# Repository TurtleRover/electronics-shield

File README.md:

<p align="center">
  
</p>
<h1 align="center">Electronics: Shield</h1>
<h4 align="center">This is Raspberry Pi 3 hat designed for Turtle rover.</h4>  

<p align="center">

</p>
<p align="center">
  <a href="http://turtlerover.com" alt="Website">Website</a> |
  <a href="https://www.facebook.com/TurtleRover/" alt="Facebook">Facebook</a> |
  <a href="https://www.youtube.com/channel/UCxukvEct3wP0S5FACa3uelA" alt="YouTube">YouTube</a>
</p>

## Specification:

Supply voltage: from 12 V to 28 V  
Equipped with TLE9201SG motor controllers  
Continuous output current per channel: 6 A  
Maximum momentary current per channel: 8 A  
Number of channels: 4  
PWM frequency: up to 20 kHz  
3 x adjustable step-down DC-DC 3A converters   
Built-in STM32F030 microprocessor  
Available interfaces:  
- I2C/UART
- SPI
- USB
- SWD
- 3 x servo

Dedicated to Raspberry Pi B + connectors  
Dimensions: 84 x 56 mm

## Board view

## Connectors standard  

| I2C & Servo  | USB & SPI | Programming  |
| ------------- | ------------- | ------------- |
|   |   |  |

## Manufacturing
Manufacture files are generated and added to release.

### Online view of schematics and layout
View this project on [CADLAB.io](https://cadlab.io/project/1250). 

This git project is intended for using with Eagle PCB.

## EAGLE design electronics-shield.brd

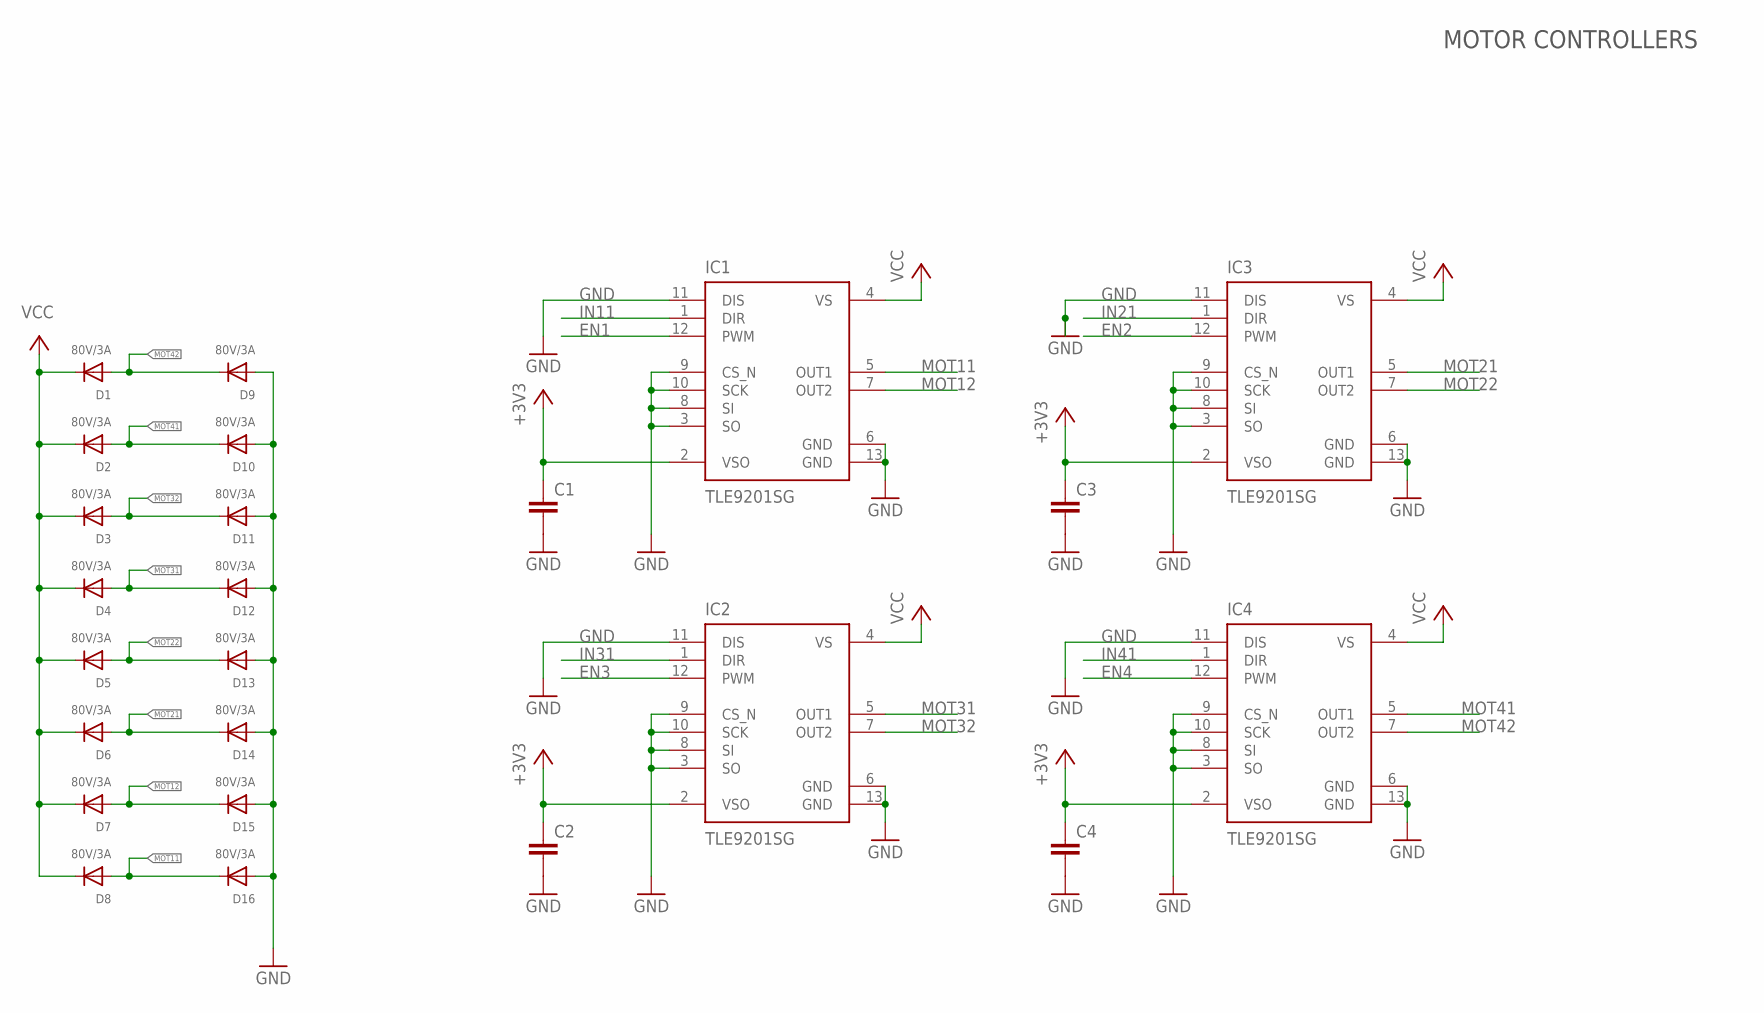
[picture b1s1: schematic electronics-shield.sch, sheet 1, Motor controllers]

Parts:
C1, C2, C3, C4: CAPACITOR_SMD_0603; C0603K
D1, D2, D3, D4, D5, D6, D7, D8, D9, D10, D11, D12, D13, D14, D15, D16: 80V/3A; SOD-123FL
IC1, IC2, IC3, IC4: TLE9201SG; PG-DSO-12-9

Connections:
+3V3: C1.1, C2.1, C3.1, C4.1, IC1.2 (VSO), IC2.2 (VSO), IC3.2 (VSO), IC4.2 (VSO); also elsewhere on the board
EN1: IC1.12 (PWM); also elsewhere on the board
EN2: IC3.12 (PWM); also elsewhere on the board
EN3: IC2.12 (PWM); also elsewhere on the board
EN4: IC4.12 (PWM); also elsewhere on the board
GND: C1.2, C2.2, C3.2, C4.2, D9.A, D10.A, D11.A, D12.A, D13.A, D14.A, D15.A, D16.A, IC1.3 (SO), IC1.6 (GND), IC1.8 (SI), IC1.9 (CS_N), IC1.10 (SCK), IC1.11 (DIS), IC1.13 (GND), IC2.3 (SO), IC2.6 (GND), IC2.8 (SI), IC2.9 (CS_N), IC2.10 (SCK), IC2.11 (DIS), IC2.13 (GND), IC3.3 (SO), IC3.6 (GND), IC3.8 (SI), IC3.9 (CS_N), IC3.10 (SCK), IC3.11 (DIS), IC3.13 (GND), IC4.3 (SO), IC4.6 (GND), IC4.8 (SI), IC4.9 (CS_N), IC4.10 (SCK), IC4.11 (DIS), IC4.13 (GND); also elsewhere on the board
IN11: IC1.1 (DIR); also elsewhere on the board
IN21: IC3.1 (DIR); also elsewhere on the board
IN31: IC2.1 (DIR); also elsewhere on the board
IN41: IC4.1 (DIR); also elsewhere on the board
MOT11: D8.A, D16.C, IC1.5 (OUT1); also elsewhere on the board
MOT12: D7.A, D15.C, IC1.7 (OUT2); also elsewhere on the board
MOT21: D6.A, D14.C, IC3.5 (OUT1); also elsewhere on the board
MOT22: D5.A, D13.C, IC3.7 (OUT2); also elsewhere on the board
MOT31: D4.A, D12.C, IC2.5 (OUT1); also elsewhere on the board
MOT32: D3.A, D11.C, IC2.7 (OUT2); also elsewhere on the board
MOT41: D2.A, D10.C, IC4.5 (OUT1); also elsewhere on the board
MOT42: D1.A, D9.C, IC4.7 (OUT2); also elsewhere on the board
VCC: D1.C, D2.C, D3.C, D4.C, D5.C, D6.C, D7.C, D8.C, IC1.4 (VS), IC2.4 (VS), IC3.4 (VS), IC4.4 (VS); also elsewhere on the board

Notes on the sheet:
MOTOR CONTROLLERS

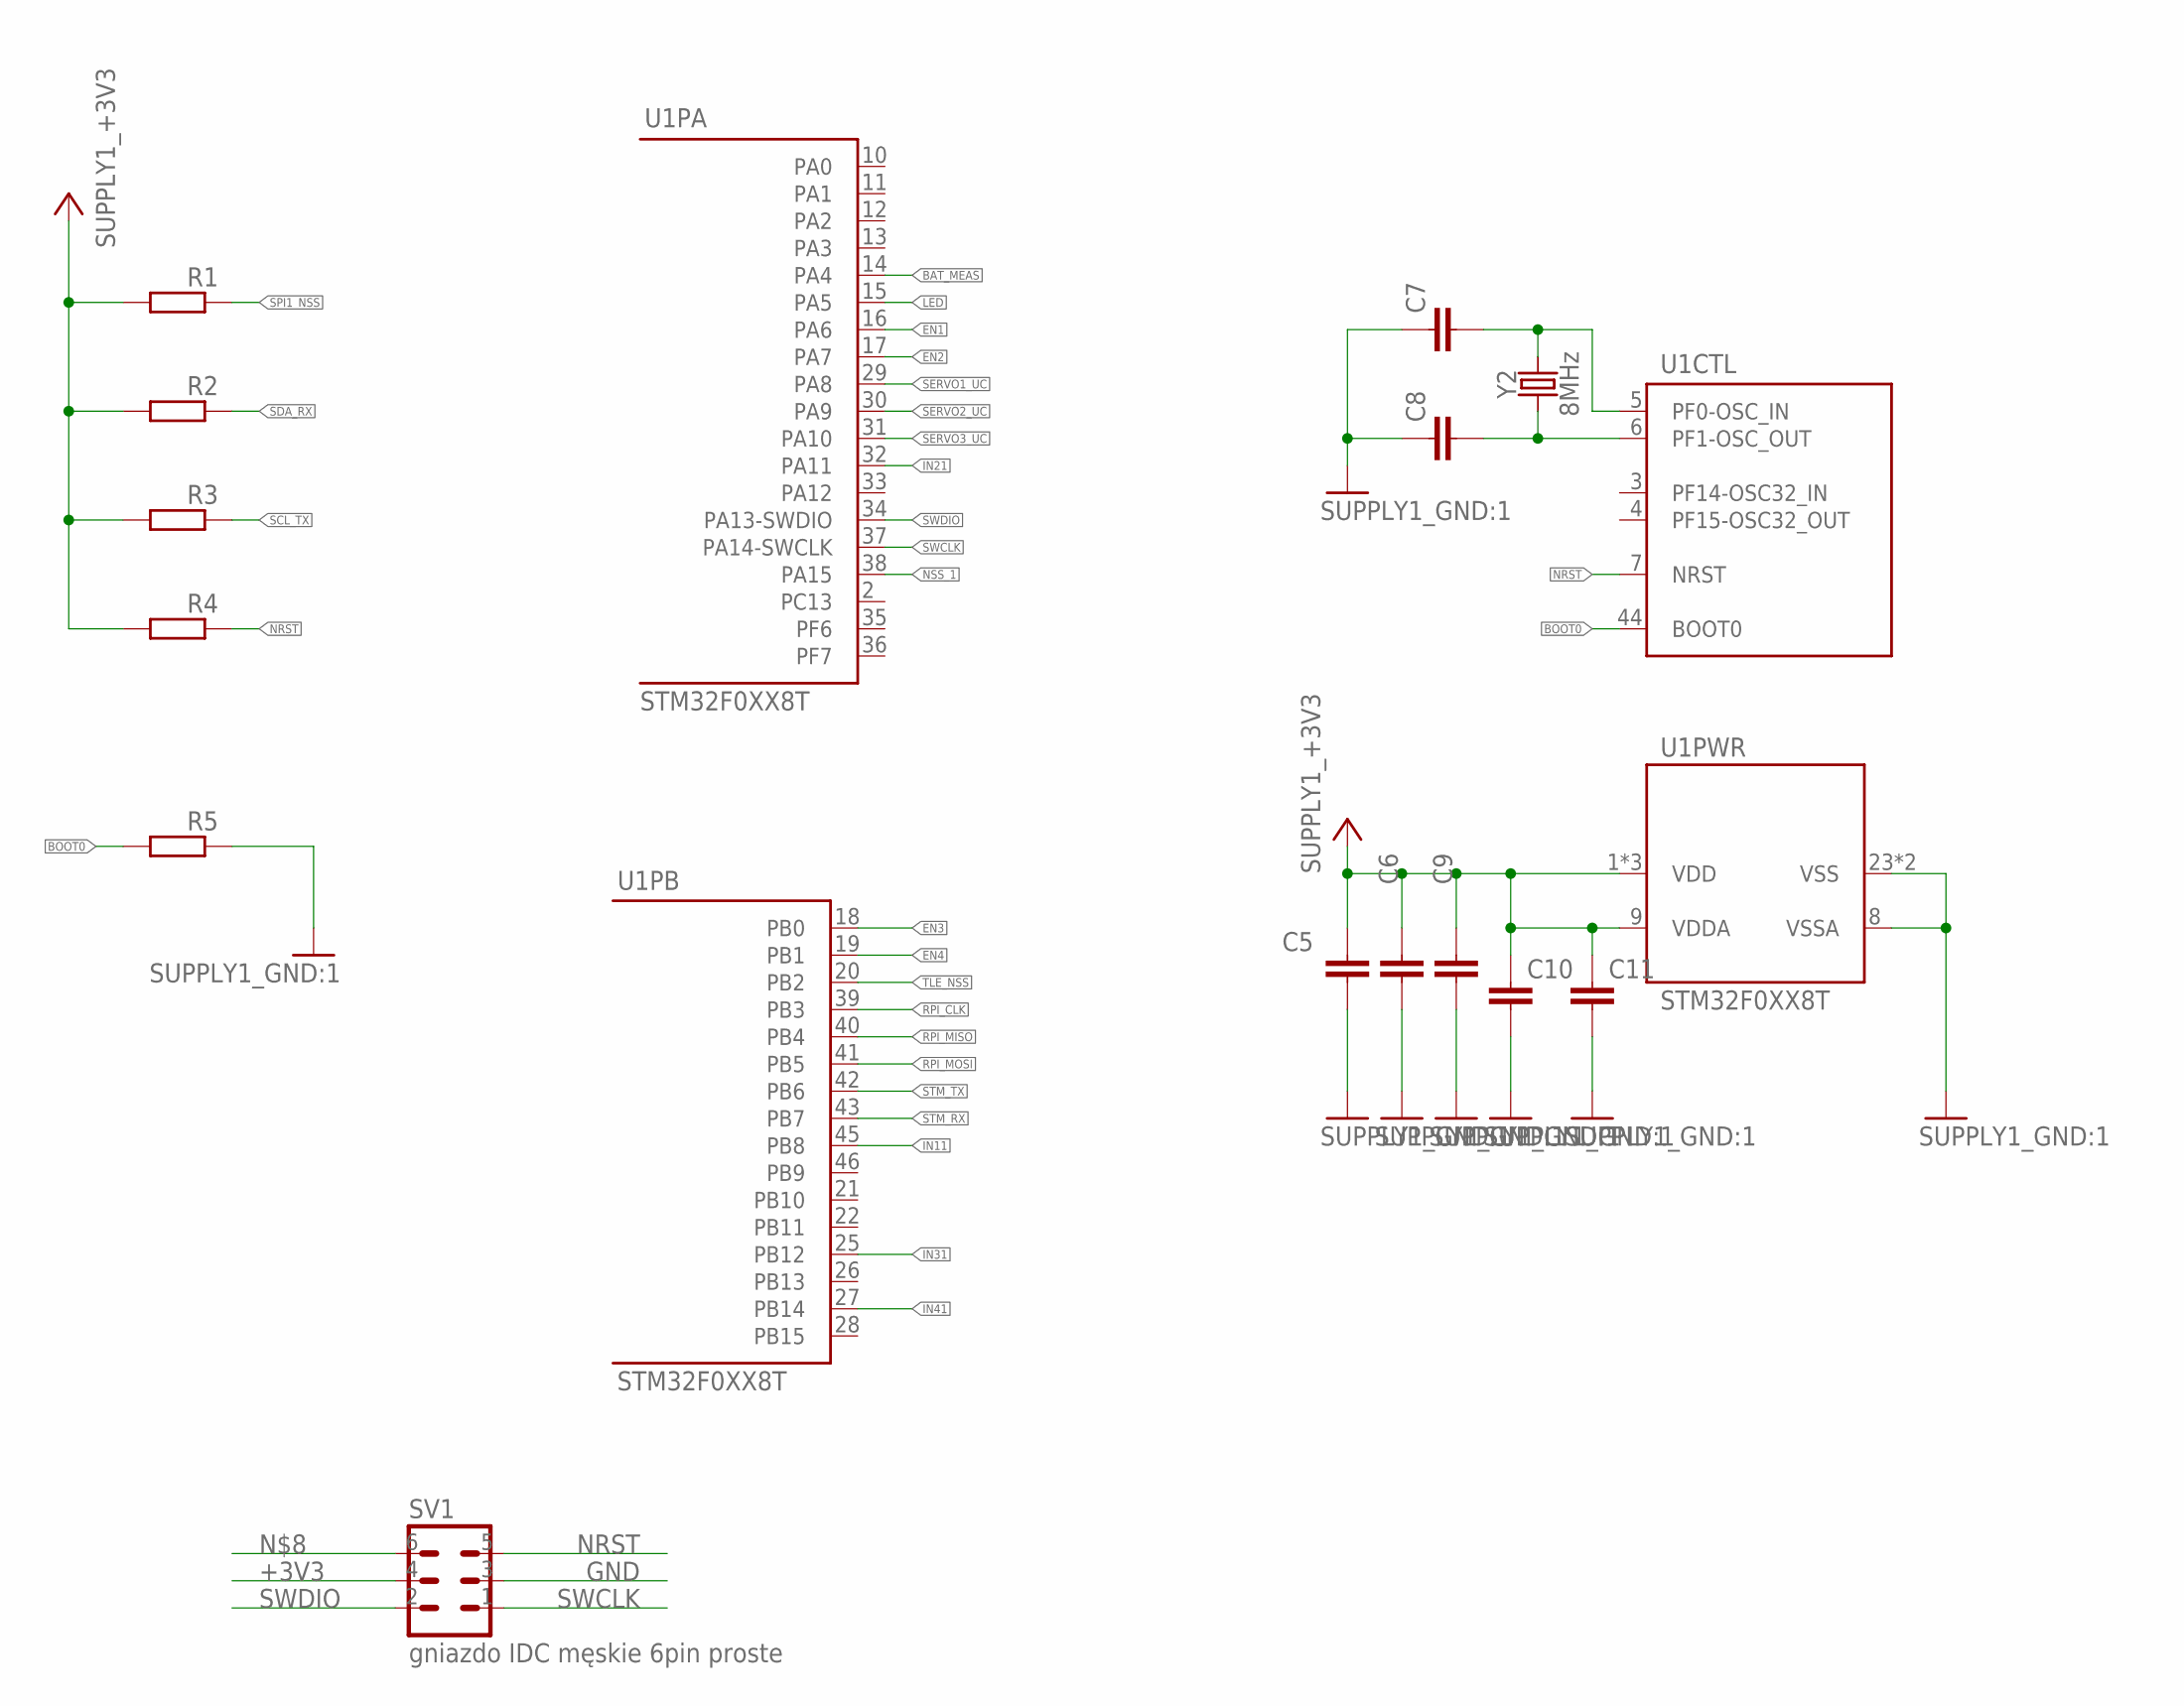
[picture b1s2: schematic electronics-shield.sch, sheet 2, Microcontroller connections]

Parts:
C5, C6, C7, C8, C9, C10, C11: CAPACITOR_SMD_0603; C0603K
R1, R2, R3, R4, R5: RESISTOR_SMD_0603; R0603
SV1: gniazdo IDC męskie 6pin proste; ML6
U1: STM32F0XX8T; LQFP48
Y2: 8MHz; CRYSTAL-SMD-5X3.2-4PAD

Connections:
+3V3: C5.1, C6.1, C9.1, C10.1, C11.1, R1.2, R2.2, R3.2, R4.2, SV1.4, U1.1 (VDD), U1.9 (VDDA), U1.24 (VDD), U1.48 (VDD); also elsewhere on the board
BAT_MEAS: U1.14 (PA4); also elsewhere on the board
BOOT0: R5.2, U1.44 (BOOT0)
EN1: U1.16 (PA6); also elsewhere on the board
EN2: U1.17 (PA7); also elsewhere on the board
EN3: U1.18 (PB0); also elsewhere on the board
EN4: U1.19 (PB1); also elsewhere on the board
GND: C5.2, C6.2, C7.1, C8.1, C9.2, C10.2, C11.2, R5.1, SV1.3, U1.8 (VSSA), U1.23 (VSS), U1.47 (VSS); also elsewhere on the board
IN11: U1.45 (PB8); also elsewhere on the board
IN21: U1.32 (PA11); also elsewhere on the board
IN31: U1.25 (PB12); also elsewhere on the board
IN41: U1.27 (PB14); also elsewhere on the board
LED: U1.15 (PA5); also elsewhere on the board
NRST: R4.1, SV1.5, U1.7 (NRST); also elsewhere on the board
NSS_1: U1.38 (PA15); also elsewhere on the board
OSCILATOR_N: C7.2, U1.5 (PF0-OSC_IN), Y2.3 (2)
OSCILATOR_P: C8.2, U1.6 (PF1-OSC_OUT), Y2.1
RPI_CLK: U1.39 (PB3); also elsewhere on the board
RPI_MISO: U1.40 (PB4); also elsewhere on the board
RPI_MOSI: U1.41 (PB5); also elsewhere on the board
SCL_TX: R3.1; also elsewhere on the board
SDA_RX: R2.1; also elsewhere on the board
SERVO1_UC: U1.29 (PA8); also elsewhere on the board
SERVO2_UC: U1.30 (PA9); also elsewhere on the board
SERVO3_UC: U1.31 (PA10); also elsewhere on the board
SPI1_NSS: R1.1
STM_RX: U1.43 (PB7); also elsewhere on the board
STM_TX: U1.42 (PB6); also elsewhere on the board
SWCLK: SV1.1, U1.37 (PA14-SWCLK); also elsewhere on the board
SWDIO: SV1.2, U1.34 (PA13-SWDIO); also elsewhere on the board
TLE_NSS: U1.20 (PB2)

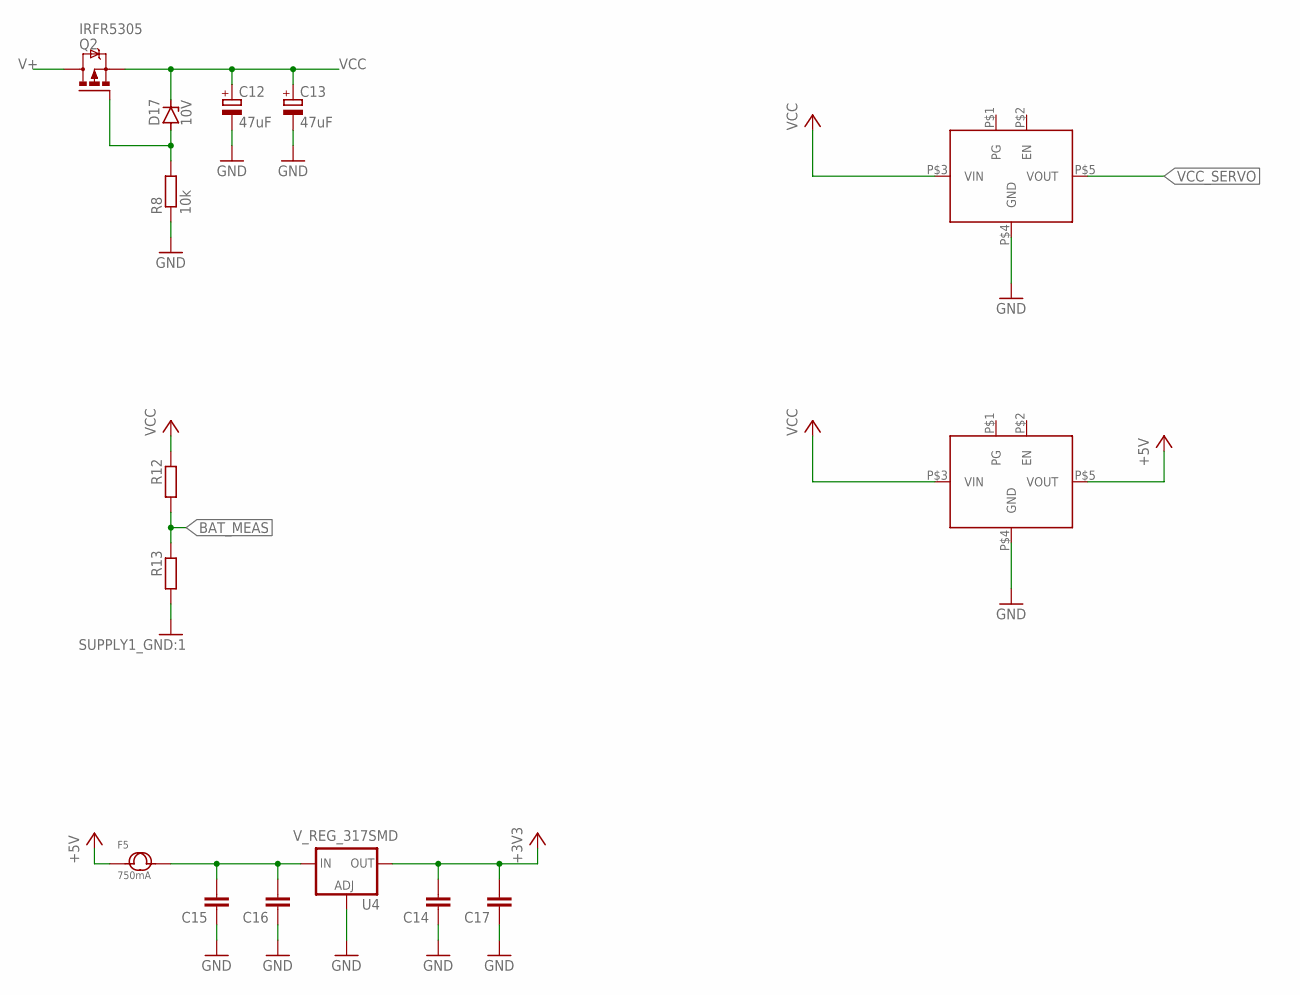
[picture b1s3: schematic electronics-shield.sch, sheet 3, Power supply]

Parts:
C12, C13: 47uF; PANASONIC_C
C14, C15, C16, C17: CAPACITOR_SMD_0603; C0603K
D17: 10V; SOD80C
F5: 750mA; F1206
Q2: IRFR5305; D-PAK_TO252AA
R8: 10k; R0603
R12, R13: RESISTOR_SMD_0603; R0603
U4: V_REG_317SMD; SOT223
U$1, U$2: POLOLU_D24V22FX

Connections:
+3V3: C14.2, C17.2, U4.2 (OUT); also elsewhere on the board
+5V: F5.1, U$2.P$5 (VOUT); also elsewhere on the board
BAT_MEAS: R12.2, R13.1; also elsewhere on the board
GND: C12.-, C13.-, C14.1, C15.1, C16.1, C17.1, R8.1, R13.2, U4.1 (ADJ), U$1.P$4 (GND), U$2.P$4 (GND); also elsewhere on the board
unnamed: D17.A, Q2.1 (G), R8.2
unnamed: C15.2, C16.2, F5.2, U4.3 (IN)
V+: Q2.4 (D); also elsewhere on the board
VCC: C12.+, C13.+, D17.C, Q2.3 (S), R12.1, U$1.P$3 (VIN), U$2.P$3 (VIN); also elsewhere on the board
VCC_SERVO: U$1.P$5 (VOUT); also elsewhere on the board

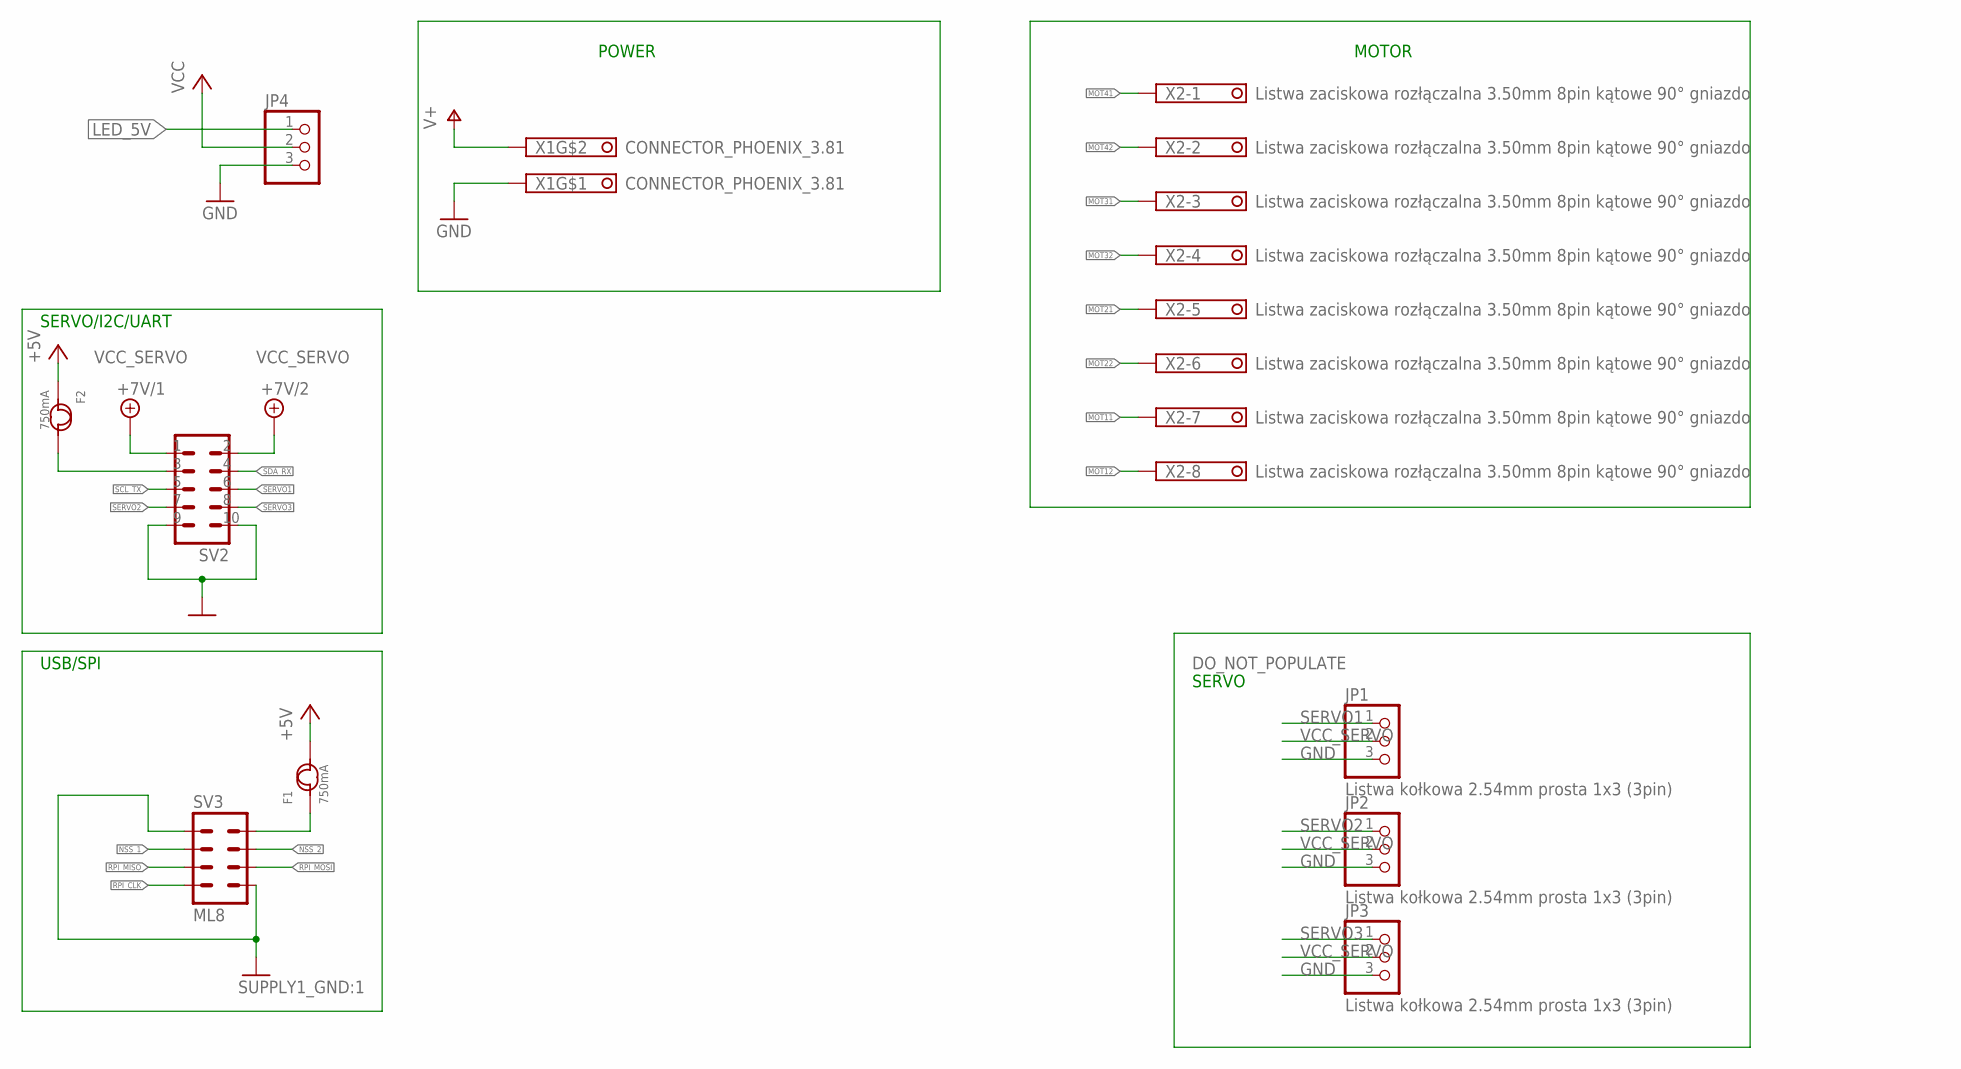
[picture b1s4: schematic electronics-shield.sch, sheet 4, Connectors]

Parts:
F1, F2: 750mA; F1206
JP1, JP2, JP3: Listwa kołkowa 2.54mm prosta 1x3 (3pin); 1X03_ROUND_DNP
JP4: PINHD-1X3; 1X03
SV2: ML10
SV3: ML8
X1: CONNECTOR_PHOENIX_3.81; 3.81MM_2PIN
X2: Listwa zaciskowa rozłączalna 3.50mm 8pin kątowe 9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; 3.5MM_8PIN

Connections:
+5V: F1.2, F2.1; also elsewhere on the board
GND: JP1.3, JP2.3, JP3.3, JP4.3, SV2.9, SV2.10, SV3.1, SV3.8, X1.1; also elsewhere on the board
LED_5V: JP4.1; also elsewhere on the board
MOT11: X2.7; also elsewhere on the board
MOT12: X2.8; also elsewhere on the board
MOT21: X2.5; also elsewhere on the board
MOT22: X2.6; also elsewhere on the board
MOT31: X2.3; also elsewhere on the board
MOT32: X2.4; also elsewhere on the board
MOT41: X2.1; also elsewhere on the board
MOT42: X2.2; also elsewhere on the board
unnamed: F2.2, SV2.3
unnamed: F1.1, SV3.2
NSS_1: SV3.3; also elsewhere on the board
NSS_2: SV3.4
RPI_CLK: SV3.7; also elsewhere on the board
RPI_MISO: SV3.5; also elsewhere on the board
RPI_MOSI: SV3.6; also elsewhere on the board
SCL_TX: SV2.5; also elsewhere on the board
SDA_RX: SV2.4; also elsewhere on the board
SERVO1: JP1.1, SV2.6; also elsewhere on the board
SERVO2: JP2.1, SV2.7; also elsewhere on the board
SERVO3: JP3.1, SV2.8; also elsewhere on the board
V+: X1.2; also elsewhere on the board
VCC: JP4.2; also elsewhere on the board
VCC_SERVO: JP1.2, JP2.2, JP3.2, SV2.1, SV2.2; also elsewhere on the board

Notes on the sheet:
SERVO
MOTOR
POWER
SERVO/I2C/UART
USB/SPI

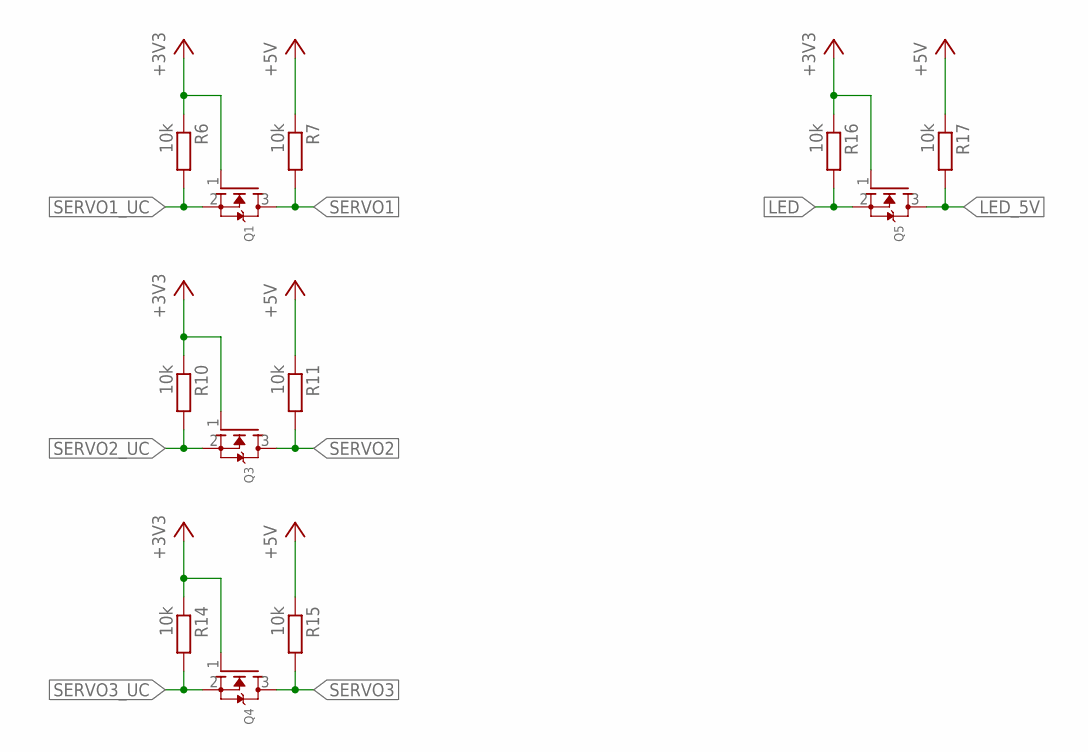
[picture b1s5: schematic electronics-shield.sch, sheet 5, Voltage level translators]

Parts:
Q1, Q3, Q4, Q5: MOSFET-NREFLOW; SOT23
R6, R7, R10, R11, R14, R15, R16, R17: 10k; R0603

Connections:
+3V3: Q1.1 (G), Q3.1 (G), Q4.1 (G), Q5.1 (G), R6.1, R10.1, R14.1, R16.1; also elsewhere on the board
+5V: R7.1, R11.1, R15.1, R17.1; also elsewhere on the board
LED: Q5.2 (S), R16.2; also elsewhere on the board
LED_5V: Q5.3 (D), R17.2; also elsewhere on the board
SERVO1: Q1.3 (D), R7.2; also elsewhere on the board
SERVO1_UC: Q1.2 (S), R6.2; also elsewhere on the board
SERVO2: Q3.3 (D), R11.2; also elsewhere on the board
SERVO2_UC: Q3.2 (S), R10.2; also elsewhere on the board
SERVO3: Q4.3 (D), R15.2; also elsewhere on the board
SERVO3_UC: Q4.2 (S), R14.2; also elsewhere on the board

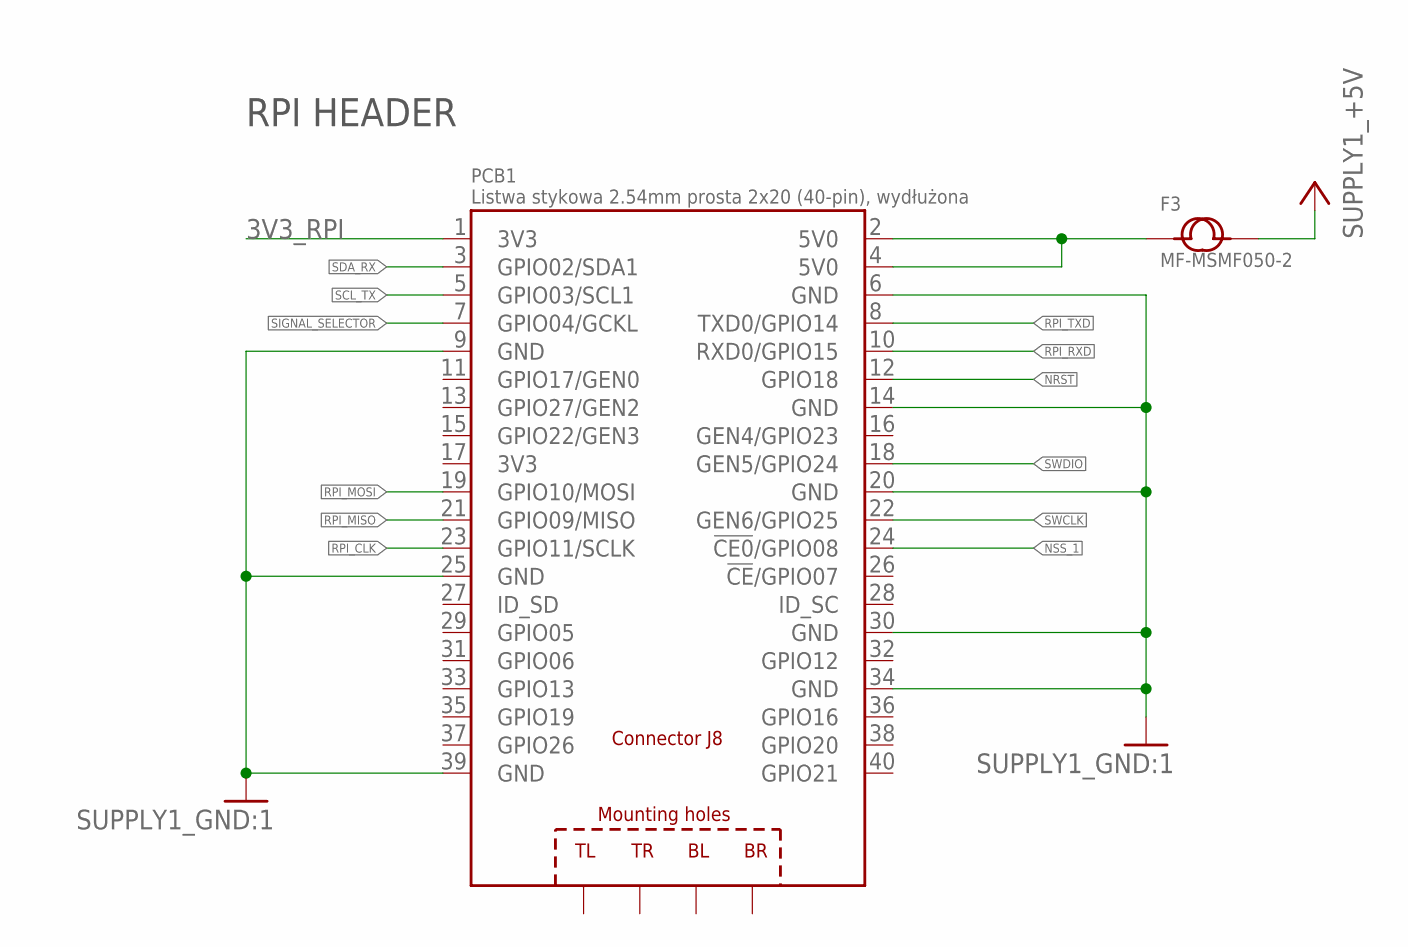
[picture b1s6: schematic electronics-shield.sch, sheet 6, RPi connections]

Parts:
F3: MF-MSMF050-2; F1812
PCB1: Listwa stykowa 2.54mm prosta 2x20 (40-pin), wydłu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; RASPBERRY_PI_B+_CONNECTOR_SMD

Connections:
3V3: PCB1.17 (3V3)
3V3_RPI: PCB1.1 (3V3)
+5V: F3.2; also elsewhere on the board
GND: PCB1.6 (GND), PCB1.9 (GND), PCB1.14 (GND), PCB1.20 (GND), PCB1.25 (GND), PCB1.30 (GND), PCB1.34 (GND), PCB1.39 (GND); also elsewhere on the board
unnamed: F3.1, PCB1.2 (5V0), PCB1.4 (5V0)
NRST: PCB1.12 (GPIO18); also elsewhere on the board
NSS_1: PCB1.24 (!CE0!/GPIO08); also elsewhere on the board
RPI_CLK: PCB1.23 (GPIO11/SCLK); also elsewhere on the board
RPI_MISO: PCB1.21 (GPIO09/MISO); also elsewhere on the board
RPI_MOSI: PCB1.19 (GPIO10/MOSI); also elsewhere on the board
RPI_RXD: PCB1.10 (RXD0/GPIO15); also elsewhere on the board
RPI_TXD: PCB1.8 (TXD0/GPIO14); also elsewhere on the board
SCL_TX: PCB1.5 (GPIO03/SCL1); also elsewhere on the board
SDA_RX: PCB1.3 (GPIO02/SDA1); also elsewhere on the board
SIGNAL_SELECTOR: PCB1.7 (GPIO04/GCKL); also elsewhere on the board
SWCLK: PCB1.22 (GEN6/GPIO25); also elsewhere on the board
SWDIO: PCB1.18 (GEN5/GPIO24); also elsewhere on the board

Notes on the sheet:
RPI HEADER

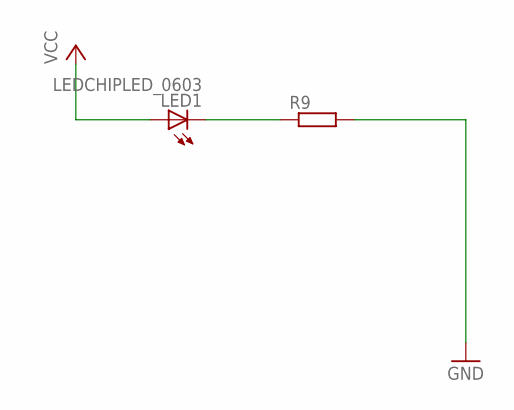
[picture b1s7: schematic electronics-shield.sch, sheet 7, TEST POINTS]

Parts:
LED1: LEDCHIPLED_0603; CHIPLED_0603
R9: RESISTOR_SMD_0603; R0603

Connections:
GND: R9.2; also elsewhere on the board
unnamed: LED1.C, R9.1
VCC: LED1.A; also elsewhere on the board

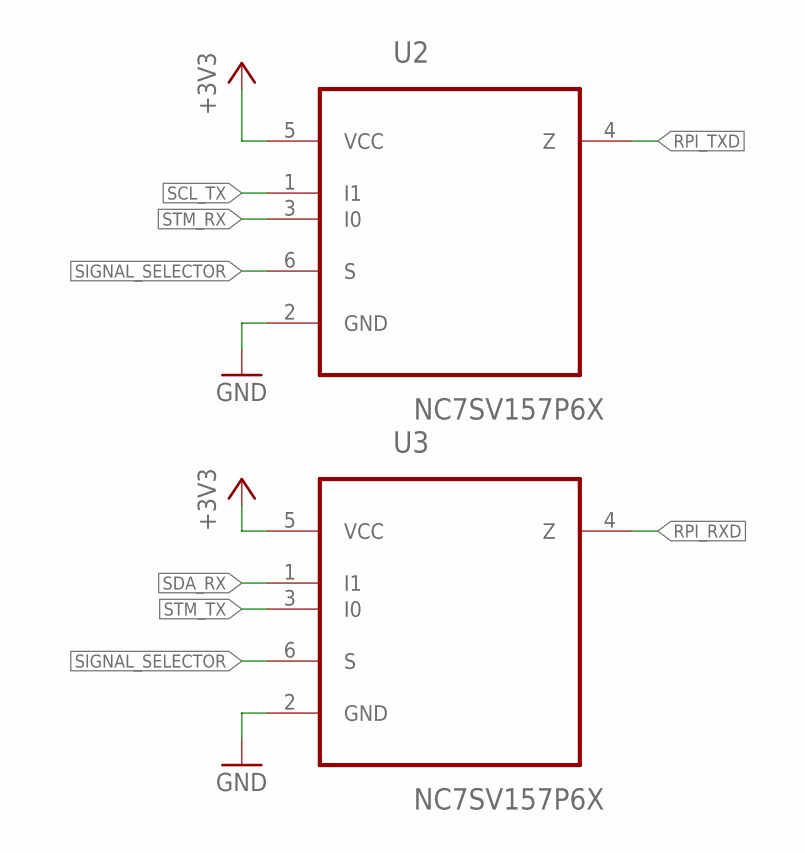
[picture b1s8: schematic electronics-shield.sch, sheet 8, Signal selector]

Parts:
U2, U3: NC7SV157P6X; SOT65P210X110-6N

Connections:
+3V3: U2.5 (VCC), U3.5 (VCC); also elsewhere on the board
GND: U2.2 (GND), U3.2 (GND); also elsewhere on the board
RPI_RXD: U3.4 (Z); also elsewhere on the board
RPI_TXD: U2.4 (Z); also elsewhere on the board
SCL_TX: U2.1 (I1); also elsewhere on the board
SDA_RX: U3.1 (I1); also elsewhere on the board
SIGNAL_SELECTOR: U2.6 (S), U3.6 (S); also elsewhere on the board
STM_RX: U2.3 (I0); also elsewhere on the board
STM_TX: U3.3 (I0); also elsewhere on the board

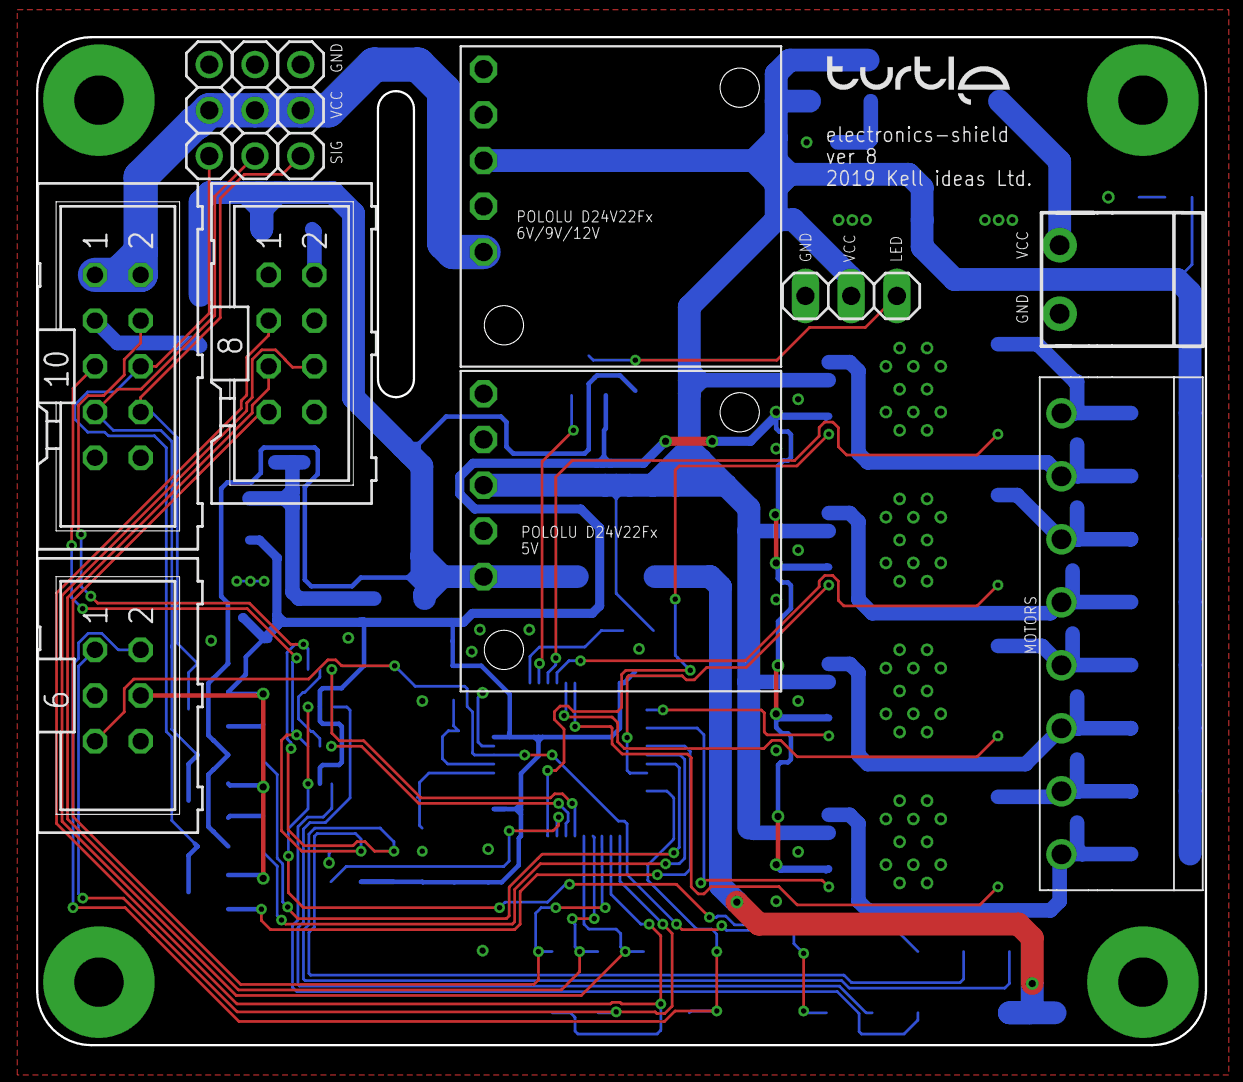
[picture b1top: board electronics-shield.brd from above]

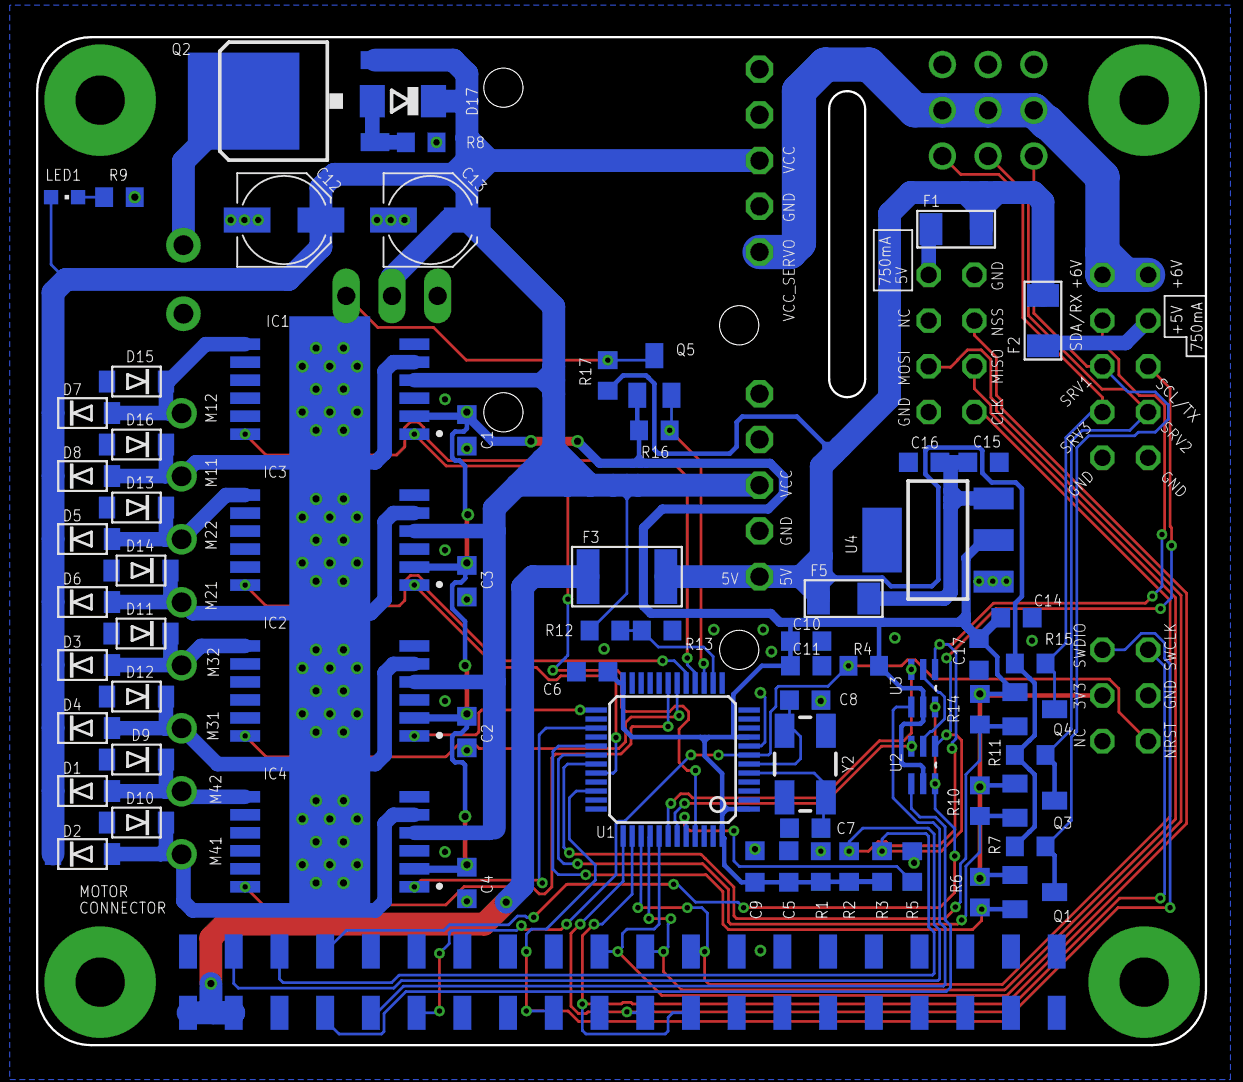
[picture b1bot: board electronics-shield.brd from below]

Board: 2 copper layers, 64.9 x 56.0 mm, 82 parts (70 on the bottom side), 54 nets.

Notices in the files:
parts and their libraries:
SparkFun-IC-Memory: Licensing: Creative Commons ShareAlike 4.0 International - https://creativecommons.org/licenses/by-sa/4.0
